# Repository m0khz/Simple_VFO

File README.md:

# Simple_VFO
Simple VFO using Si5351 &amp; custom hardware.

A comprehensive video build of this project is available here:

https://youtu.be/oWSVf3w8YGg

The 2.2" tft module uses the ILI9341 driver there are different versions out there and the pinout changes,

 *                            - the boards have been designed for this type:
 *                            - https://www.elektor.com/2-2-spi-tft-display-module-240x320 
 *                            - I bought mine from eBay

The Teensy 3.2 module available from https://www.pjrc.com/store/teensy32.html 

 *                            - I bought mine from eBay

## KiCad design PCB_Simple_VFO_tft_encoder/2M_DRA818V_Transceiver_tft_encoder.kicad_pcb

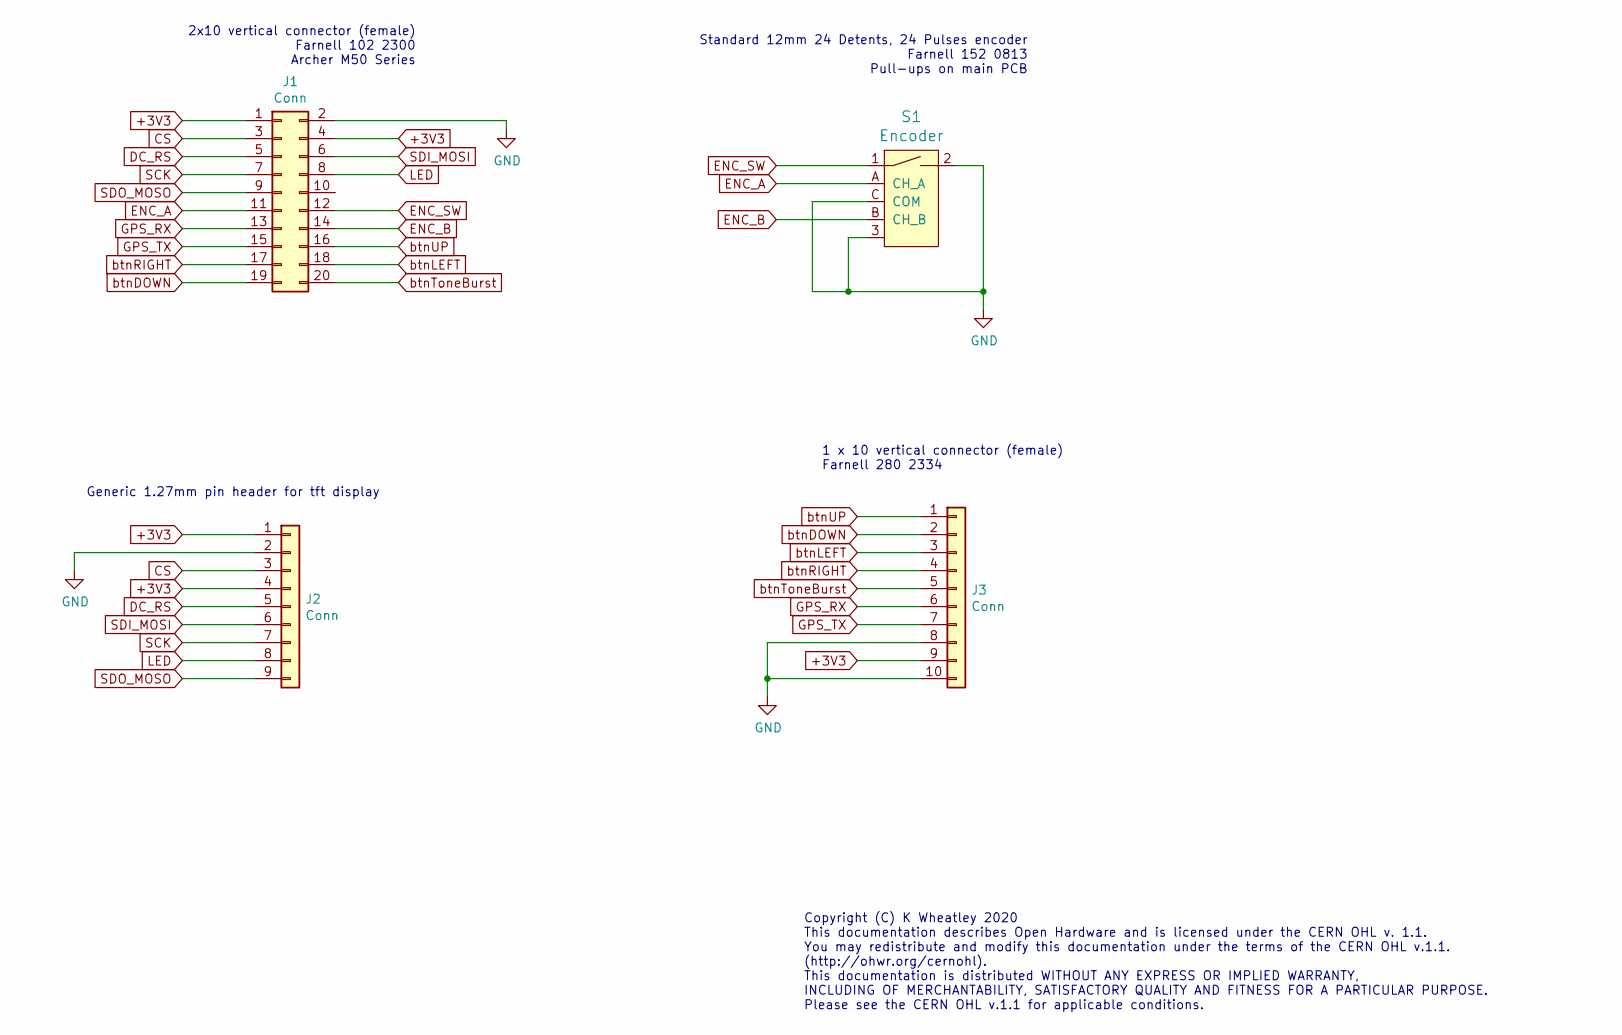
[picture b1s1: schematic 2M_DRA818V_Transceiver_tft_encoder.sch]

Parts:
J1: Conn; PinHeader_2x10_P2.54mm_Vertical
J2: Conn; PinHeader_1x09_P2.54mm_Vertical
J3: Conn; PinHeader_1x10_P2.54mm_Vertical
S1: Encoder; Rotary_Encoder_Switched_PEC11R; MPN PEC11R-4215F-S0024; Digi-Key_PN PEC11R-4215F-S0024-ND

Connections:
+3V3: J1.1, J1.4, J2.1, J2.4, J3.9
CS: J1.3, J2.3
DC_RS: J1.5, J2.5
ENC_A: J1.11, S1.A (CH_A)
ENC_B: J1.14, S1.B (CH_B)
ENC_SW: J1.12, S1.1
GND: J1.2, J2.2, J3.8, J3.10, S1.2, S1.3, S1.C (COM)
GPS_RX: J1.13, J3.6
GPS_TX: J1.15, J3.7
LED: J1.8, J2.8
SCK: J1.7, J2.7
SDI_MOSI: J1.6, J2.6
SDO_MOSO: J1.9, J2.9
btnDOWN: J1.19, J3.2
btnLEFT: J1.18, J3.3
btnRIGHT: J1.17, J3.4
btnToneBurst: J1.20, J3.5
btnUP: J1.16, J3.1

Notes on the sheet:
2x10 vertical connector (female) Farnell 102 2300 Archer M50 Series
Generic 1.27mm pin header for tft display
Standard 12mm 24 Detents, 24 Pulses encoder Farnell 152 0813 Pull-ups on main PCB
Copyright (C) K Wheatley 2020 This documentation describes Open Hardware and is licensed under the CERN OHL v. 1.1. You may redistribute and modify this documentation under the terms of the CERN OHL v.1.1. (http://ohwr.org/cernohl). This documentation is distributed WITHOUT ANY EXPRESS OR IMPLIED W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
1 x 10 vertical connector (female) Farnell 280 2334

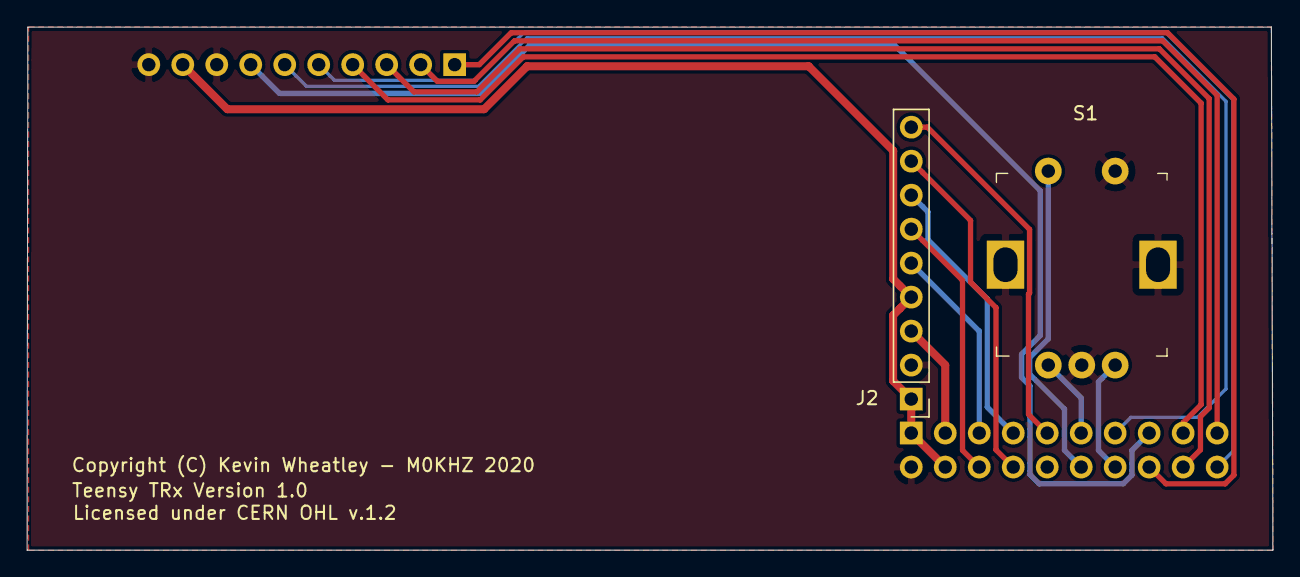
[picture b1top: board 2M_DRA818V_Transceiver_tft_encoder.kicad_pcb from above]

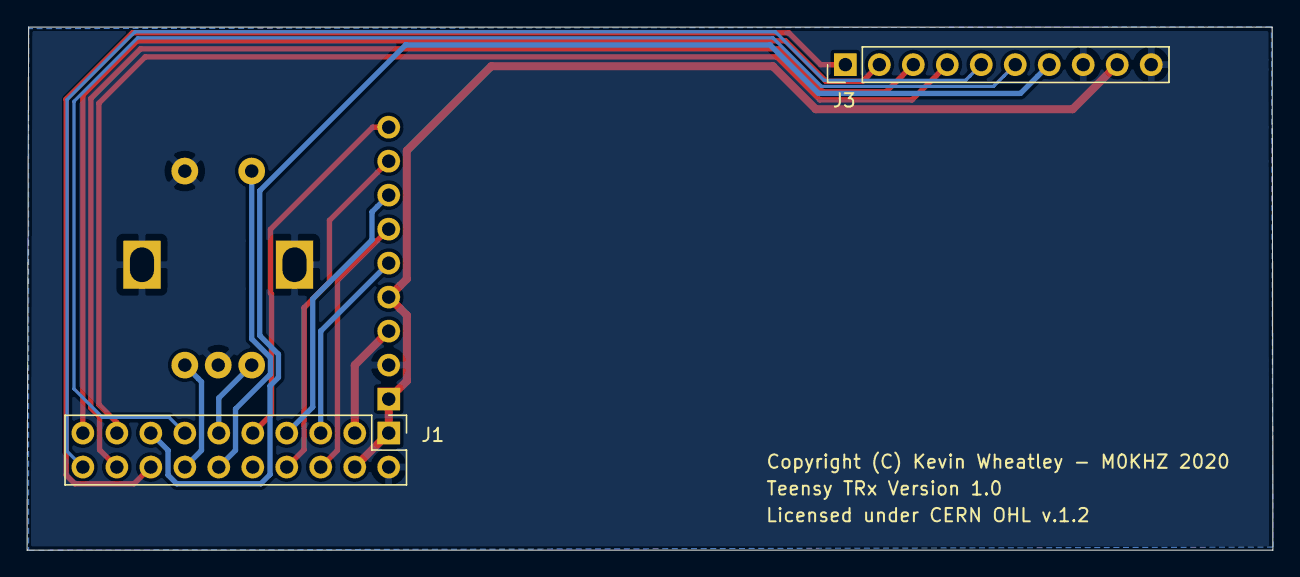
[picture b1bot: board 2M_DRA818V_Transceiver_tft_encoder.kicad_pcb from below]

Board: 2 copper layers, 93.1 x 39.1 mm, 4 parts (2 on the bottom side), 18 nets.

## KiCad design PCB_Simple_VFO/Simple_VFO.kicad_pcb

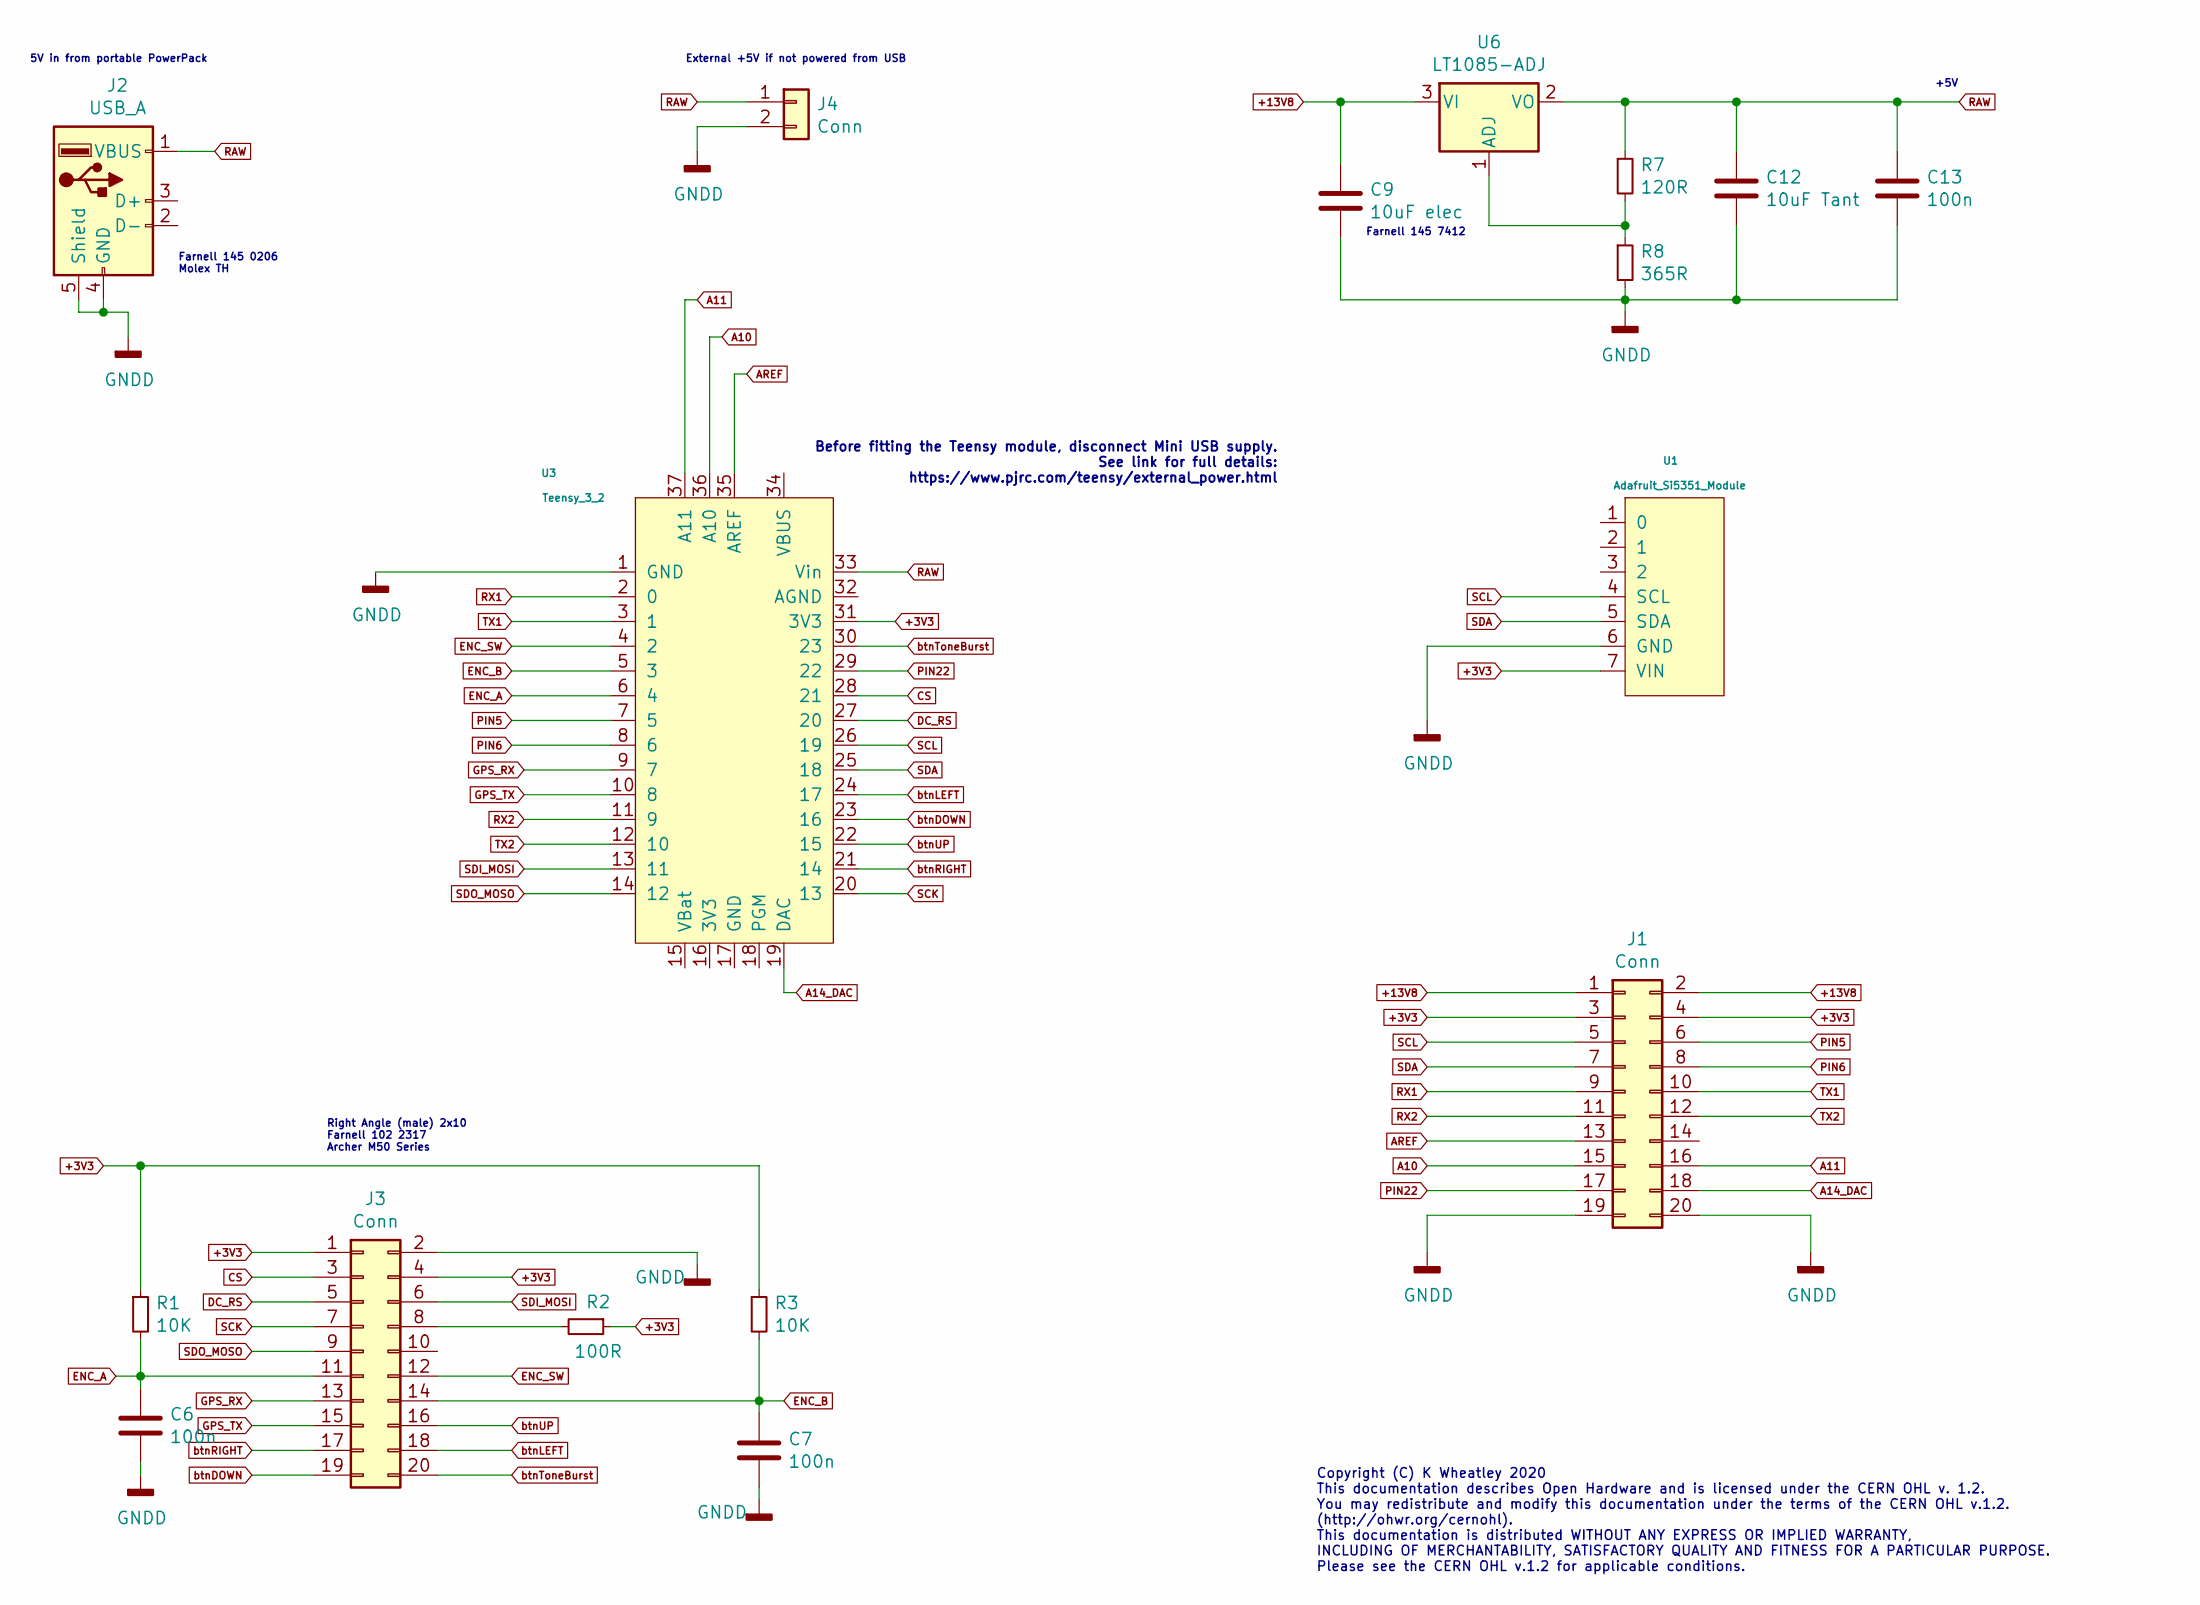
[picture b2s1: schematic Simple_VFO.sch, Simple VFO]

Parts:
C6, C7, C13: 100n; C_0603_1608Metric_Pad1.05x0.95mm_HandSolder
C9: 10uF elec; CP_EIA-3216-12_Kemet-S_Pad1.58x1.35mm_HandSolder
C12: 10uF Tant; CP_EIA-3216-12_Kemet-S_Pad1.58x1.35mm_HandSolder
J1, J3: Conn; PinHeader_2x10_P2.54mm_Horizontal
J2: USB_A; USB_A_Stewart_SS-52100-001_Horizontal
J4: Conn; PinHeader_1x02_P2.54mm_Vertical
R1, R3: 10K; C_0603_1608Metric_Pad1.05x0.95mm_HandSolder
R2: 100R; C_0603_1608Metric_Pad1.05x0.95mm_HandSolder
R7: 120R; C_0603_1608Metric_Pad1.05x0.95mm_HandSolder
R8: 365R; C_0603_1608Metric_Pad1.05x0.95mm_HandSolder
U1: Adafruit_Si5351_Module
U3: Teensy_3_2
U6: LT1085-ADJ; TO-263-3_TabPin2

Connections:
+3V3: J1.3, J1.4, J3.1, J3.4, R1.1, R2.1, R3.1, U1.7 (VIN), U3.31 (3V3)
+13V8: C9.1, J1.1, J1.2, U6.3 (VI)
A10: J1.15, U3.36 (A10)
A11: J1.16, U3.37 (A11)
A14_DAC: J1.18, U3.19 (DAC)
AREF: J1.13, U3.35 (AREF)
CS: J3.3, U3.28 (21)
DC_RS: J3.5, U3.27 (20)
ENC_A: C6.2, J3.11, R1.2, U3.6 (4)
ENC_B: C7.2, J3.14, R3.2, U3.5 (3)
ENC_SW: J3.12, U3.4 (2)
GNDD: C6.1, C7.1, C9.2, C12.2, C13.1, J1.19, J1.20, J2.4 (GND), J2.5 (Shield), J3.2, J4.2, R8.2, U1.6 (GND), U3.1 (GND)
GPS_RX: J3.13, U3.9 (7)
GPS_TX: J3.15, U3.10 (8)
unnamed: J3.8, R2.2
unnamed: R7.2, R8.1, U6.1 (ADJ)
PIN5: J1.6, U3.7 (5)
PIN6: J1.8, U3.8 (6)
PIN22: J1.17, U3.29 (22)
RAW: C12.1, C13.2, J2.1 (VBUS), J4.1, R7.1, U3.33 (Vin), U6.2 (VO)
RX1: J1.9, U3.2 (0)
RX2: J1.11, U3.11 (9)
SCK: J3.7, U3.20 (13)
SCL: J1.5, U1.4 (SCL), U3.26 (19)
SDA: J1.7, U1.5 (SDA), U3.25 (18)
SDI_MOSI: J3.6, U3.13 (11)
SDO_MOSO: J3.9, U3.14 (12)
TX1: J1.10, U3.3 (1)
TX2: J1.12, U3.12 (10)
btnDOWN: J3.19, U3.23 (16)
btnLEFT: J3.18, U3.24 (17)
btnRIGHT: J3.17, U3.21 (14)
btnToneBurst: J3.20, U3.30 (23)
btnUP: J3.16, U3.22 (15)

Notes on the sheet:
5V in from portable PowerPack
Right Angle (male) 2x10 Farnell 102 2317 Archer M50 Series
Farnell 145 7412
Farnell 145 0206 Molex TH
Before fitting the Teensy module, disconnect Mini USB supply. See link for full details: https://www.pjrc.com/teensy/external_power.html
Copyright (C) K Wheatley 2020 This documentation describes Open Hardware and is licensed under the CERN OHL v. 1.2. You may redistribute and modify this documentation under the terms of the CERN OHL v.1.2. (http://ohwr.org/cernohl). This documentation is distributed WITHOUT ANY EXPRESS OR IMPLIED W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
External +5V if not powered from USB
+5V

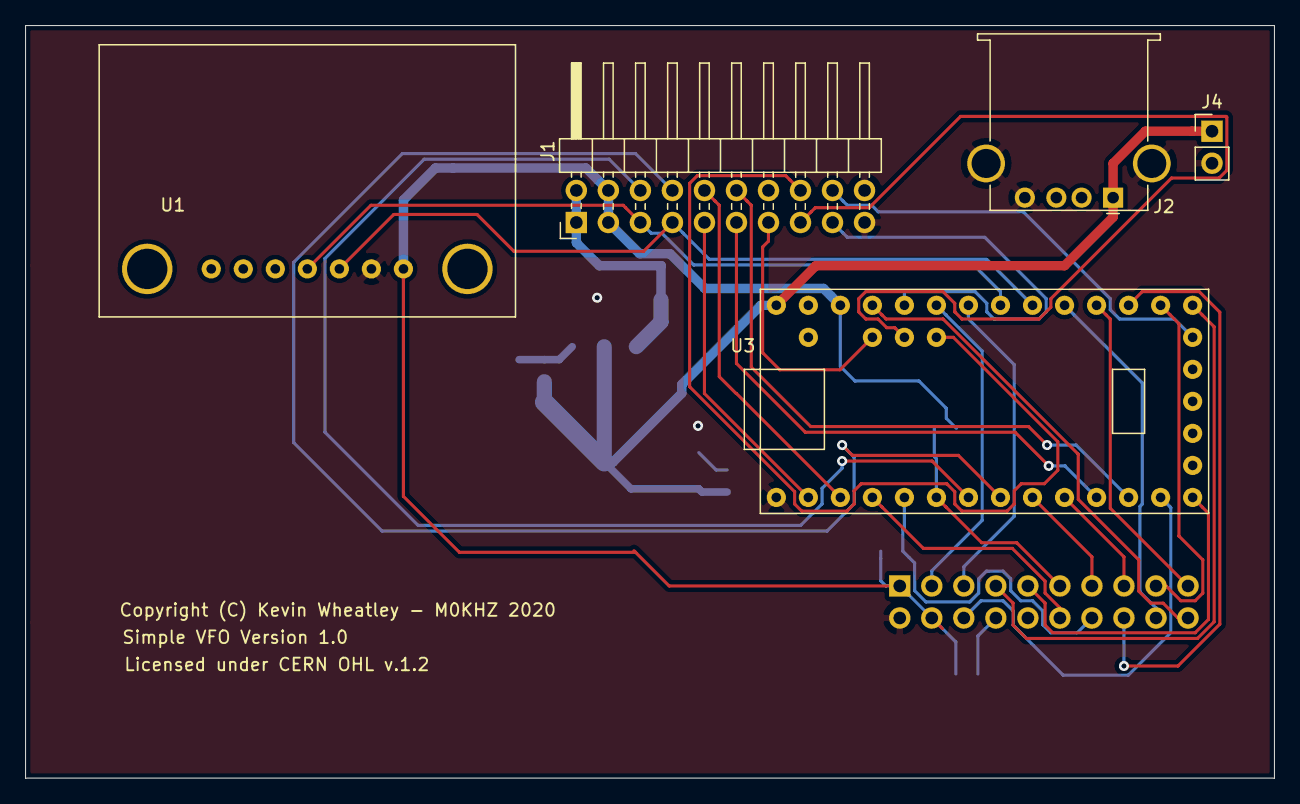
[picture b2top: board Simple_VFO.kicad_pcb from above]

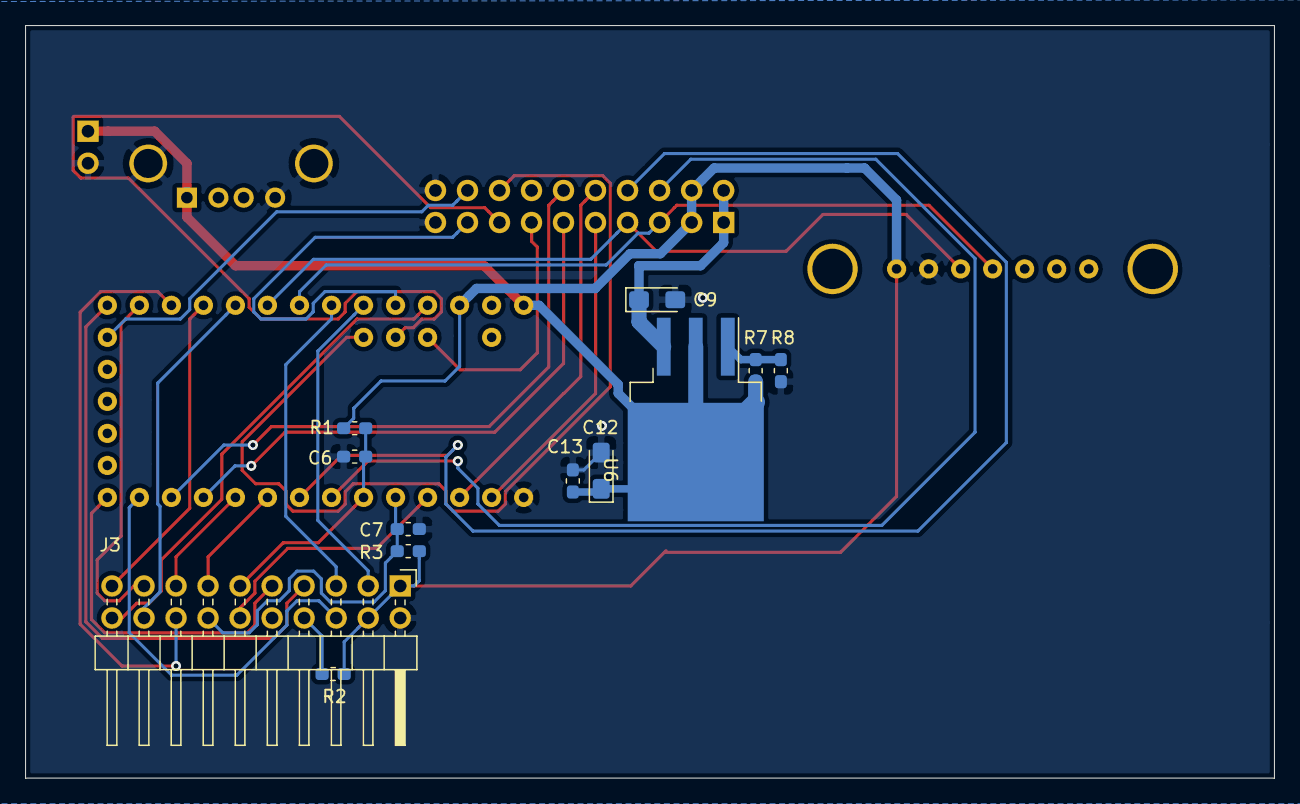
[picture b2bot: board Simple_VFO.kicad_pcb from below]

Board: 2 copper layers, 99.1 x 59.7 mm, 17 parts (12 on the bottom side), 34 nets.

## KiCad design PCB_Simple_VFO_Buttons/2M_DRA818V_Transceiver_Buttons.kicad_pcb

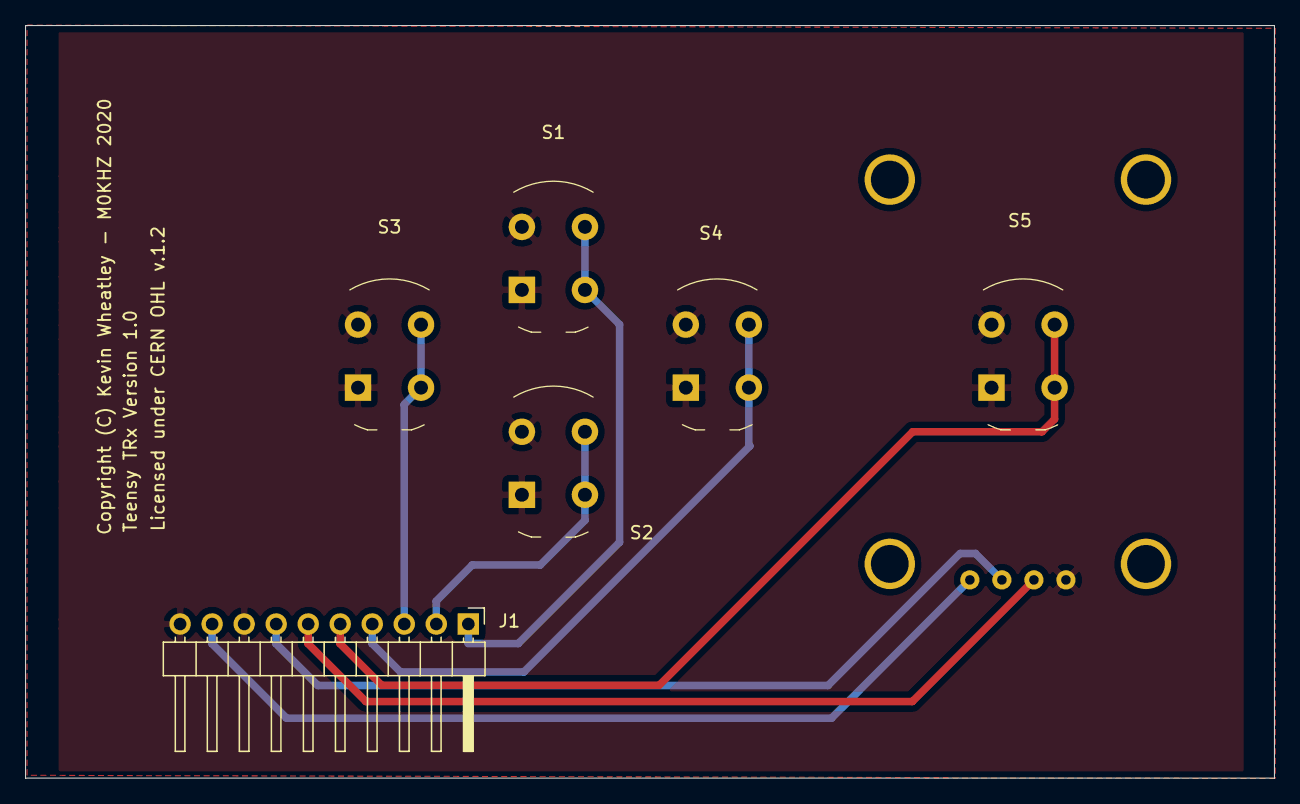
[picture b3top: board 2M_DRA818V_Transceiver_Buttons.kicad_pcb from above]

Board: 2 copper layers, 99.1 x 59.7 mm, 7 parts (1 on the bottom side), 9 nets.

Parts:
J1: Conn; PinHeader_1x10_P2.54mm_Horizontal
S1: btn_UP; PushButton_Round_D12mm_THT_KS-01Q-01
S2: btn_DOWN; PushButton_Round_D12mm_THT_KS-01Q-01
S3: btn_LEFT; PushButton_Round_D12mm_THT_KS-01Q-01
S4: btn_RIGHT; PushButton_Round_D12mm_THT_KS-01Q-01
S5: btn_ToneBurst; PushButton_Round_D12mm_THT_KS-01Q-01
U1: GY-GPS6MV2; UBlox_GY-GPS6MV2

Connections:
+3V3: J1.9, U1.4
GND: J1.8, J1.10, S1.1, S1.3, S2.1, S2.3, S3.1, S3.3, S4.1, S4.3, S5.1, S5.3, U1.1
GPS_RX: J1.6, U1.2
GPS_TX: J1.7, U1.3
btnDOWN: J1.2, S2.2, S2.4
btnLEFT: J1.3, S3.2, S3.4
btnRIGHT: J1.4, S4.2, S4.4
btnToneBurst: J1.5, S5.2, S5.4
btnUP: J1.1, S1.2, S1.4

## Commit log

2020-05-19 Initial Release
2021-03-23 Typo fixed
2021-05-14 Added Text

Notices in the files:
PCB_Simple_VFO/Simple_VFO.kicad_pcb:
Licensed under CERN OHL v.1.2
Copyright (C) Kevin Wheatley - M0KHZ 2020
